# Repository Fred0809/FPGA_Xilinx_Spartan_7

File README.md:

# Spartan 7 Dev Board
4 layer pcb for Xilinx Spartan 7 FPGA. Includes USB connector, FTDI USB bridge chip, IMU, 2 PMOD conenctors, plus LEDs and buttons.

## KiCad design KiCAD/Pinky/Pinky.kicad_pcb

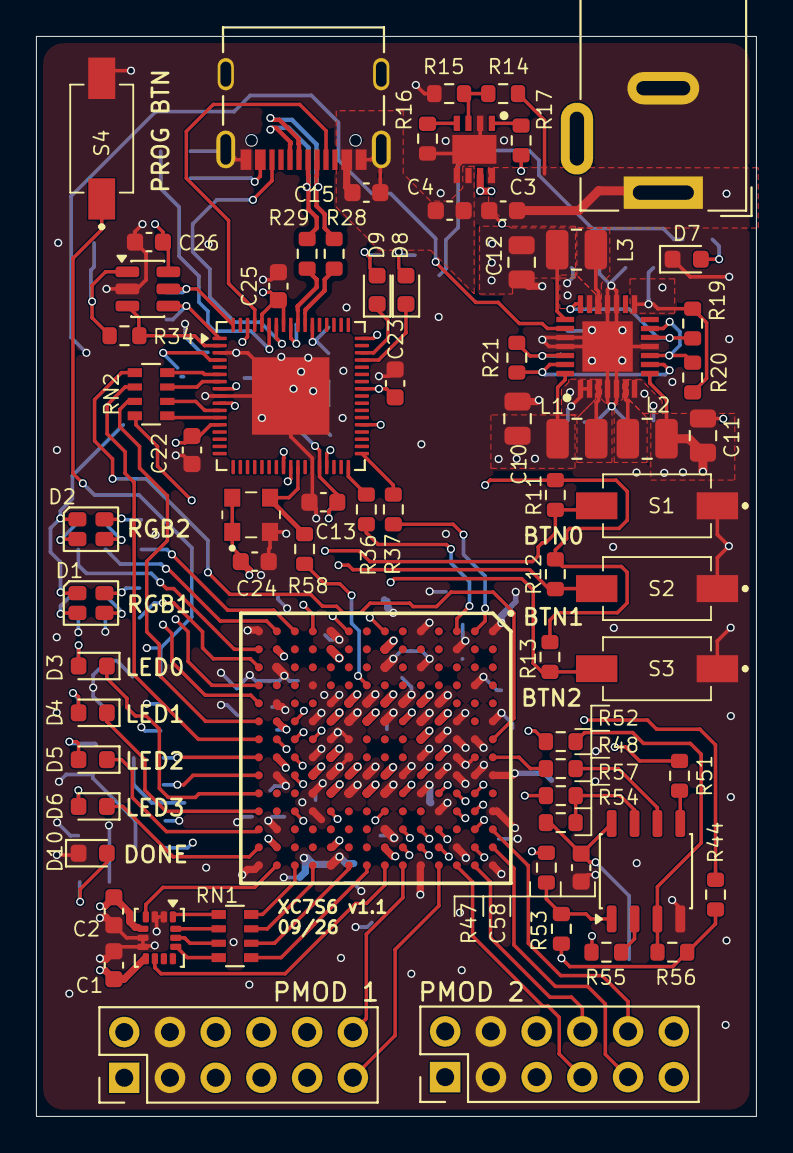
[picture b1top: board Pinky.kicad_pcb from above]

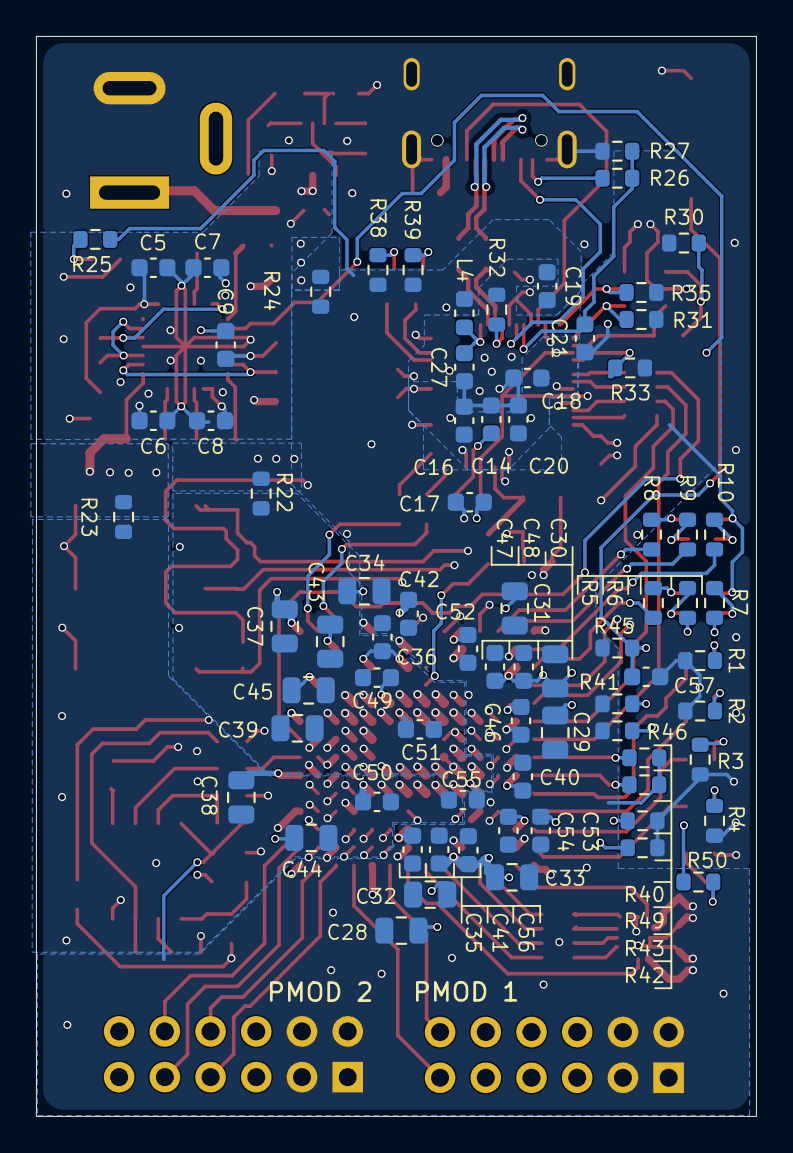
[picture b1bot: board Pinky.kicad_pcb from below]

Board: 4 copper layers, 40.0 x 60.0 mm, 147 parts (75 on the bottom side), 123 nets.

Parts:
C1, C2, C3, C4, C13, C14, C17, C18, C19, C20, C22, C23, C25, C26, C57, C58: 100n; C_0603_1608Metric
C5, C6, C7, C8: 2u2; C_0603_1608Metric
C9, C15: 1u; C_0603_1608Metric
C10, C11, C12: 22u; C_0805_2012Metric
C16: 4u7; C_0603_1608Metric
C21: 33n; C_0603_1608Metric
C24: 10n; C_0603_1608Metric
C27, C35, C36, C40, C41, C42, C46, C47, C48, C49, C50, C51, C52, C53, C54, C55, C56: 470n; C_0603_1608Metric
C28, C38, C39: 47u; C_0805_2012Metric
C29, C30, C31, C32, C33, C34, C43, C44, C45: 4u7; C_0805_2012Metric
C37: 100u; C_0805_2012Metric
D1, D2: LED_ARGB; LED_Cree-PLCC4_2x2mm_CW_copy
D3, D4, D5, D6, D7, D8, D9, D10: LED 0603; LED_0603_1608Metric
J1, J2: Pmod; PinHeader_2x06_P2.54mm_Vertical
J4: USB C connector; AMPHENOL_12402012E212A
J5: Barrel_Jack_MountingPin; BarrelJack_Wuerth_6941xx301002
L1, L2, L3: 1u5; L_1008_2520Metric
L4: 100R@100MHz; L_0603_1608Metric
PS1: TPS2113; TPS2115APW-SON65P300X300X100-9N-D
R1, R2, R3, R4, R5, R6, R7, R8, R9, R10: 180R; R_0603_1608Metric
R11, R12, R13, R17, R30, R31, R35: 10k; R_0603_1608Metric
R14, R27: 15k; R_0603_1608Metric
R15: 5k; R_0603_1608Metric
R16, R38, R39: 470R; R_0603_1608Metric
R19, R20, R21: 20k; R_0603_1608Metric
R22, R23, R24: 0R; R_0603_1608Metric
R25, R34: 2k2; R_0603_1608Metric
R26: 100k; R_0603_1608Metric
R28, R29, R36, R37: 10R; R_0603_1608Metric
R32: 12k/1%; R_0603_1608Metric
R33, R40, R45, R46, R53, R56, R57: 4k7; R_0603_1608Metric
R41, R42, R43, R44: 1k; R_0603_1608Metric
R47, R48, R50, R51, R52, R54, R55: 100R; R_0603_1608Metric
R49: 200R; R_0603_1608Metric
R58: 50R; R_0603_1608Metric
RN1, RN2: Resistor network 0603; R_Array_Convex_4x0603
S1, S2, S3, S4: 434121025816; 434121050816
U1: LSM6DS3; LGA-14_3x2.5mm_P0.5mm_LayoutBorder3x4y
U2: XC7S6-2FTGB196C; XC7S6-2FTGB196C-BGA196C100P14X14_1500X1500X155
U3: MAX20029ATIA_V+; MAX20029-QFN50P500X500X80-29N
U4: 93LC66BT-E/OT; SOT-23-6
U5: FT2232HPQ; VQFN-68-1EP_8x8mm_P0.4mm_EP4.3x4.3mm
U6: MX25L3233FM1; JEITA_SOIC-8_3.9x4.9mm_P1.27mm
Y1: 12MHz; ASEMB

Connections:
+1V0: C37.2, C39.2, C43.2, C45.2, C49.2, C51.2, R22.1, U2.D6 (VCCINT), U2.D8 (VCCINT), U2.E5 (VCCBRAM), U2.E7 (VCCINT), U2.E9 (VCCINT), U2.F6 (VCCINT), U2.G5 (VCCBRAM), U2.G9 (VCCINT), U2.H6 (VCCINT), U2.J5 (VCCBRAM), U2.J9 (VCCINT), U2.K6 (VCCINT), U2.K8 (VCCINT)
+1V8: C38.2, C44.2, C50.2, C55.2, R23.1, U2.F10 (VCCAUX), U2.H10 (VCCAUX), U2.K10 (VCCAUX), U2.L9 (VCCAUX)
+3V3: C1.2, C2.2, C13.2, C14.2, C17.2, C19.2, C22.2, C24.2, C25.2, C26.2, C28.2, C29.2, C30.2, C31.2, C32.2, C33.2, C34.2, C35.2, C36.2, C40.2, C41.2, C42.2, C46.2, C47.2, C48.2, C52.2, C53.2, C54.2, C56.2, C58.2, D1.1 (A), D2.1 (A), J1.1, J1.2, J2.1, J2.2, L4.2, R11.1, R12.1, R13.1, R24.1, R25.2, R30.1, R31.1, R33.2, R35.1, R38.1, R39.1, R40.1, R41.1, R44.1, R45.1, R46.2, R49.1, R53.1, R56.1, R57.1, U1.5 (VDDIO), U1.8 (VDD), U2.G2 (VCCO_34), U2.G13 (VCCO_14), U2.K2 (VCCO_34), U2.K13 (VCCO_14), U2.N2 (VCCO_34), U2.N6 (VCCO_0), U2.N8 (VCCO_0), U2.N13 (VCCO_14), U4.6 (VCC), U5.10 (VCCIO), U5.13 (ADBUS4), U5.26 (VCCIO), U5.30 (VREGIN), U5.39 (VCCIO), U5.51 (VCCIO), U5.61 (VCC_PD), U5.64 (PD1_VCONN), U6.8 (VCC), Y1.1 (STANDBY), Y1.4 (VDD)
+5V0: C5.2, C6.2, C7.2, C8.2, C9.2, PS1.7 (OUT), R17.2, R19.2, R20.2, R21.2, U3.1 (EN1), U3.2 (PV), U3.7 (PV2), U3.15 (PV3), U3.20 (PV4), U3.26 (VA)
+VUSB: C4.2, C15.2, J4.A4_B9 (USBVCC), J4.B4_A9 (USBVCC), PS1.6 (IN2), R26.1
/FPGA_Banks/BTN_0: R11.2, S1.2, U2.L1 (IO_L18N_T2_34)
/FPGA_Banks/BTN_1: R12.2, S2.2, U2.J1 (IO_L15N_T2_DQS_34)
/FPGA_Banks/BTN_2: R13.2, S3.2, U2.G1 (IO_L9P_T1_DQS_34)
/FPGA_Banks/LED_0: D3.1 (K), U2.P10 (IO_L24P_T3_D17_14)
/FPGA_Banks/LED_1: D4.1 (K), U2.P11 (IO_L24N_T3_D16_14)
/FPGA_Banks/LED_2: D5.1 (K), U2.P12 (IO_L22P_T3_D21_14)
/FPGA_Banks/LED_3: D6.1 (K), U2.P13 (IO_L22N_T3_D20_14)
/FPGA_Banks/RGB1_B: R7.1, U2.P5 (IO_L24P_T3_34)
/FPGA_Banks/RGB1_G: R6.1, U2.P4 (IO_L21P_T3_DQS_34)
/FPGA_Banks/RGB1_R: R5.1, U2.P3 (IO_L21N_T3_DQS_34)
/FPGA_Banks/RGB2_B: R10.1, U2.P2 (IO_L20P_T3_34)
/FPGA_Banks/RGB2_G: R9.1, U2.N1 (IO_L20N_T3_34)
/FPGA_Banks/RGB2_R: R8.1, U2.M1 (IO_L18P_T2_34)
/FPGA_Config/CFGBVS: R46.1, U2.N7 (CFGBVS_0)
/FPGA_Config/CS_RES: R47.1, U2.C11 (IO_L6P_T0_FCS_B_14)
/FPGA_Config/D00_MOSI: R51.2, U2.B11 (IO_L1P_T0_D00_MOSI_14)
/FPGA_Config/D01_DIN: R55.2, U2.B12 (IO_L1N_T0_D01_DIN_14)
/FPGA_Config/D02: R52.2, U2.D10 (IO_L2P_T0_D02_14)
/FPGA_Config/D03: R54.2, U2.C10 (IO_L2N_T0_D03_14)
/FPGA_Config/DONE: R49.2, R50.1, U2.P9 (DONE_0)
/FPGA_Config/DONE_LED: D10.2 (A), R50.2
/FPGA_Config/HOLD: R54.1, R57.2, U6.7 (~HOLD/SIO3)
/FPGA_Config/INIT: R40.2, U2.P8 (INIT_B_0)
/FPGA_Config/MODE0: R41.2, U2.M7 (M0_0)
/FPGA_Config/MODE1: R42.2, U2.M8 (M1_0)
/FPGA_Config/MODE2: R43.2, U2.M9 (M2_0)
/FPGA_Config/PROG: C57.2, R45.2, S4.1, U2.L7 (PROGRAM_B_0)
/FPGA_Config/PUDC_B: R44.2, U2.B10 (IO_L3P_T0_DQS_PUDC_B_14)
/FPGA_Config/QSPI_CS: R47.2, R53.2, U6.1 (~CS)
/FPGA_Config/QSPI_SCK: R48.1, U6.6 (SCLK)
/FPGA_Config/SCK_RES: R48.2, U2.A8 (CCLK_0)
/FPGA_Config/SI: R51.1, U6.5 (SI/SIO0)
/FPGA_Config/SO: R55.1, U6.2 (SO/SIO1)
/FPGA_Config/WP: R52.1, R56.2, U6.3 (~WP/SIO2)
/IMU/CS: RN1.4 (R4.1), U1.12 (CS)
/IMU/SCLK: RN1.3 (R3.1), U1.13 (SCL)
/IMU/SDI: RN1.2 (R2.1), U1.14 (SDA)
/IMU/SDO: RN1.1 (R1.1), U1.1 (SDO/SA0)
/Power/ILIM: PS1.4 (ILIM), R16.2
/Power/LX1: L1.1, U3.3 (LX1)
/Power/LX2: L2.1, U3.6 (LX2)
/Power/LX4: L3.1, U3.19 (LX4)
/Power/OUTS1: C10.2, L1.2, R22.2, U3.28 (OUTS1)
/Power/OUTS2: C11.2, L2.2, R23.2, U3.8 (OUTS2)
/Power/OUTS4: C12.2, L3.2, R24.2, U3.22 (OUTS4)
/Power/PG1: R21.1, U3.9 (EN2), U3.27 (PG1)
/Power/PG2: R20.1, U3.10 (PG2), U3.13 (EN3)
/Power/PG3: R19.1, U3.12 (PG3), U3.21 (EN4)
/Power/STAT: PS1.1 (STAT), R17.1
/Power/VSNS: PS1.3 (VSNS), R14.1, R15.2
/USB/CLK: R31.2, U4.4 (CLK), U5.1 (EECLK)
/USB/CS: R35.2, U4.5 (CS), U5.68 (EECS)
/USB/DI: R34.1, U4.3 (DI), U5.2 (EEDATA)
/USB/DO: R30.2, R34.2, U4.1 (DO)
/USB/LED1: D8.1 (K), U5.48 (BCBUS3)
/USB/LED1_RES: D8.2 (A), R38.2
/USB/LED2: D9.1 (K), U5.49 (BCBUS4)
/USB/LED2_RES: D9.2 (A), R39.2
/USB/PD1_CC1: J4.A5 (CC1_A), U5.65 (PD1_CC1)
/USB/PD1_CC2: J4.B5 (CC1_B), U5.62 (PD1_CC2)
/USB/PD1_SVBUS: C21.2, R26.2, R27.1, U5.63 (PD1_SVBUS)
/USB/REF: R32.1, U5.60 (REF)
/USB/TCK_RES: RN2.8 (R1.2), U5.6 (ADBUS0)
/USB/TDI_RES: RN2.7 (R2.2), U5.7 (ADBUS1)
/USB/TDO_RES: RN2.6 (R3.2), U5.11 (ADBUS2)
/USB/TMS_RES: RN2.5 (R4.2), U5.12 (ADBUS3)
/USB/UART_RX: R37.2, U5.35 (BDBUS1)
/USB/UART_TX: R36.2, U5.34 (BDBUS0)
D+: R29.1, U5.59 (DP)
D-: R28.1, U5.58 (DM)
GND: C1.1, C2.1, C3.1, C4.1, C5.1, C6.1, C7.1, C8.1, C9.1, C10.1, C11.1, C12.1, C13.1, C14.1, C15.1, C16.1, C17.1, C18.1, C19.1, C20.1, C21.1, C22.1, C23.1, C24.1, C25.1, C26.1, C27.1, C28.1, C29.1, C30.1, C31.1, C32.1, C33.1, C34.1, C35.1, C36.1, C37.1, C38.1, C39.1, C40.1, C41.1, C42.1, C43.1, C44.1, C45.1, C46.1, C47.1, C48.1, C49.1, C50.1, C51.1, C52.1, C53.1, C54.1, C55.1, C56.1, C57.1, C58.1, D7.1 (K), D10.1 (K), J1.3, J1.4, J2.3, J2.4, J4.A1_B12 (GND), J4.B1_A12 (GND), J4.SH1 (SHIELD), J4.SH2 (SHIELD), J4.SH3 (SHIELD), J4.SH4 (SHIELD), J5.2, PS1.2 (/EN), PS1.5 (GND), PS1.9 (GND_2), R1.1, R2.1, R3.1, R4.1, R15.1, R16.1, R27.2, R32.2, R42.1, R43.1, S1.1, S2.1, S3.1, S4.2, U1.2 (SDX), U1.3 (SCX), U1.6 (GND), U1.7 (GND), U2.A1 (GND), U2.A6 (GND_2), U2.A9 (GND_3), U2.A11 (GND_4), U2.A14 (GND_5), U2.B4 (GND_6), U2.B7 (GND_7), U2.B8 (VCCBATT), U2.B9 (GND_8), U2.C2 (GND_9), U2.C6 (GND_10), U2.C7 (GND_11), U2.C8 (GND_12), U2.C9 (GND_13), U2.C13 (GND_14), U2.D5 (GND_15), U2.D7 (GND_16), U2.D9 (GND_17), U2.D11 (GND_18), U2.E1 (GND_19), U2.E3 (GND_20), U2.E6 (GND_21), U2.E8 (GND_22), U2.E10 (GND_23), U2.E14 (GND_24), U2.F5 (GND_25), U2.F9 (GND_26), U2.G3 (GND_27), U2.G6 (GND_28), U2.G10 (GND_29), U2.G12 (GND_30), U2.H5 (GND_31), U2.H9 (GND_32), U2.J6 (GND_33), U2.J7 (DXN_0), U2.J8 (DXP_0), U2.J10 (GND_34), U2.K1 (GND_35), U2.K5 (GND_36), U2.K7 (GND_37), U2.K9 (GND_38), U2.K14 (GND_39), U2.L4 (GND_40), U2.L6 (GND_41), U2.L8 (GND_42), U2.L10 (GND_43), U2.L11 (GND_44), U2.N3 (GND_45), U2.N5 (GND_46), U2.N9 (GND_47), U2.N12 (GND_48), U2.P1 (GND_49), U2.P14 (GND_50), U3.4 (PGND1), U3.5 (PGND2), U3.11 (GND), U3.17 (PGND3), U3.18 (PGND4), U3.24 (GND_2), U3.25 (SYNC), U3.29 (GND_3), U4.2 (GND), U5.3 (TEST), U5.9 (GND), U5.29 (GND), U5.69 (GND), U6.4 (GND), Y1.2 (GND)
IMU_INT1: U1.4 (INT1), U2.N14 (IO_L21P_T3_DQS_14)
IMU_INT2: U1.9 (INT2), U2.G14 (IO_L9P_T1_DQS_14)
IMU_SPI_CS: RN1.5 (R4.2), U2.H14 (IO_L14N_T2_SRCC_14)
IMU_SPI_SCLK: RN1.6 (R3.2), U2.J14 (IO_L18N_T2_D27_14)
IMU_SPI_SDI: RN1.7 (R2.2), U2.L14 (IO_L15N_T2_DQS_DOUT_CSO_B_14)
IMU_SPI_SDO: RN1.8 (R1.2), U2.M14 (IO_L21N_T3_DQS_D22_14)
unnamed: D1.4 (BK), R7.2
unnamed: D1.3 (GK), R6.2
unnamed: D1.2 (RK), R5.2
unnamed: D2.4 (BK), R10.2
unnamed: D2.3 (GK), R9.2
unnamed: D2.2 (RK), R8.2
unnamed: D3.2 (A), R1.2
unnamed: D4.2 (A), R2.2
unnamed: D5.2 (A), R3.2
unnamed: D6.2 (A), R4.2
unnamed: D7.2 (A), R25.1
unnamed: R58.2, U5.27 (OSCI), Y1.3 (OUTPUT)
PG4: R33.1, U3.23 (PG4), U5.4 (~RESET)
PMOD1_1: J1.12, U2.D13 (IO_L8N_T1_D12_14)
PMOD1_2: J1.10, U2.A12 (IO_L4P_T0_D04_14)
PMOD1_3: J1.8, U2.B14 (IO_L5N_T0_D07_14)
PMOD1_4: J1.6, U2.D12 (IO_L8P_T1_D11_14)
PMOD1_5: J1.11, U2.B13 (IO_L5P_T0_D06_14)
PMOD1_6: J1.9, U2.A13 (IO_L4N_T0_D05_14)
PMOD1_7: J1.7, U2.C14 (IO_L11N_T1_SRCC_14)
PMOD1_8: J1.5, U2.E13 (IO_L10N_T1_D15_14)
PMOD2_1: J2.12, U2.F14 (IO_L9N_T1_DQS_D13_14)
PMOD2_2: J2.10, U2.F13 (IO_L10P_T1_D14_14)
PMOD2_3: J2.8, U2.G11 (IO_L12P_T1_MRCC_14)
PMOD2_4: J2.6, U2.M11 (IO_L20P_T3_D24_14)
PMOD2_5: J2.11, U2.D14 (IO_L11P_T1_SRCC_14)
PMOD2_6: J2.9, U2.E12 (IO_L7N_T1_D10_14)
PMOD2_7: J2.7, U2.F12 (IO_L7P_T1_D09_14)
PMOD2_8: J2.5, U2.K11 (IO_L19P_T3_D26_14)
PWR: C27.2, L4.1, U5.57 (VCC_USB)
SYSCLK12MHz: R58.1, U2.H4 (IO_L13P_T2_MRCC_34)
TCK: RN2.1 (R1.1), U2.A7 (TCK_0)
TDI_FPGA: RN2.2 (R2.1), U2.P7 (TDI_0)
TDO_FPGA: RN2.3 (R3.1), U2.P6 (TDO_0)
TMS: RN2.4 (R4.1), U2.M6 (TMS_0)
UART_RXD_OUT: R37.1, U2.B1 (IO_L5N_T0_34)
UART_TXD_IN: R36.1, U2.C1 (IO_L11N_T1_SRCC_34)
USBD+: J4.A6 (D+_A), J4.B6 (D+_B), R29.2
USBD-: J4.A7 (D-_A), J4.B7 (D-_B), R28.2
VCC: C3.2, J5.1, PS1.8 (IN1), R14.2
VCORE: C16.2, C18.2, C20.2, C23.2, U5.8 (VCORE), U5.25 (VCORE), U5.31 (VREGOUT), U5.44 (VCORE), U5.66 (VCORE)
